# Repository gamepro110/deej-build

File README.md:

# deej-build

| dir | what |
| --- | --- |
| [pcb](<./pcb/>) | pcb design files |
| [µ code](<./µ code/>) | code for the µ (micro) controller |

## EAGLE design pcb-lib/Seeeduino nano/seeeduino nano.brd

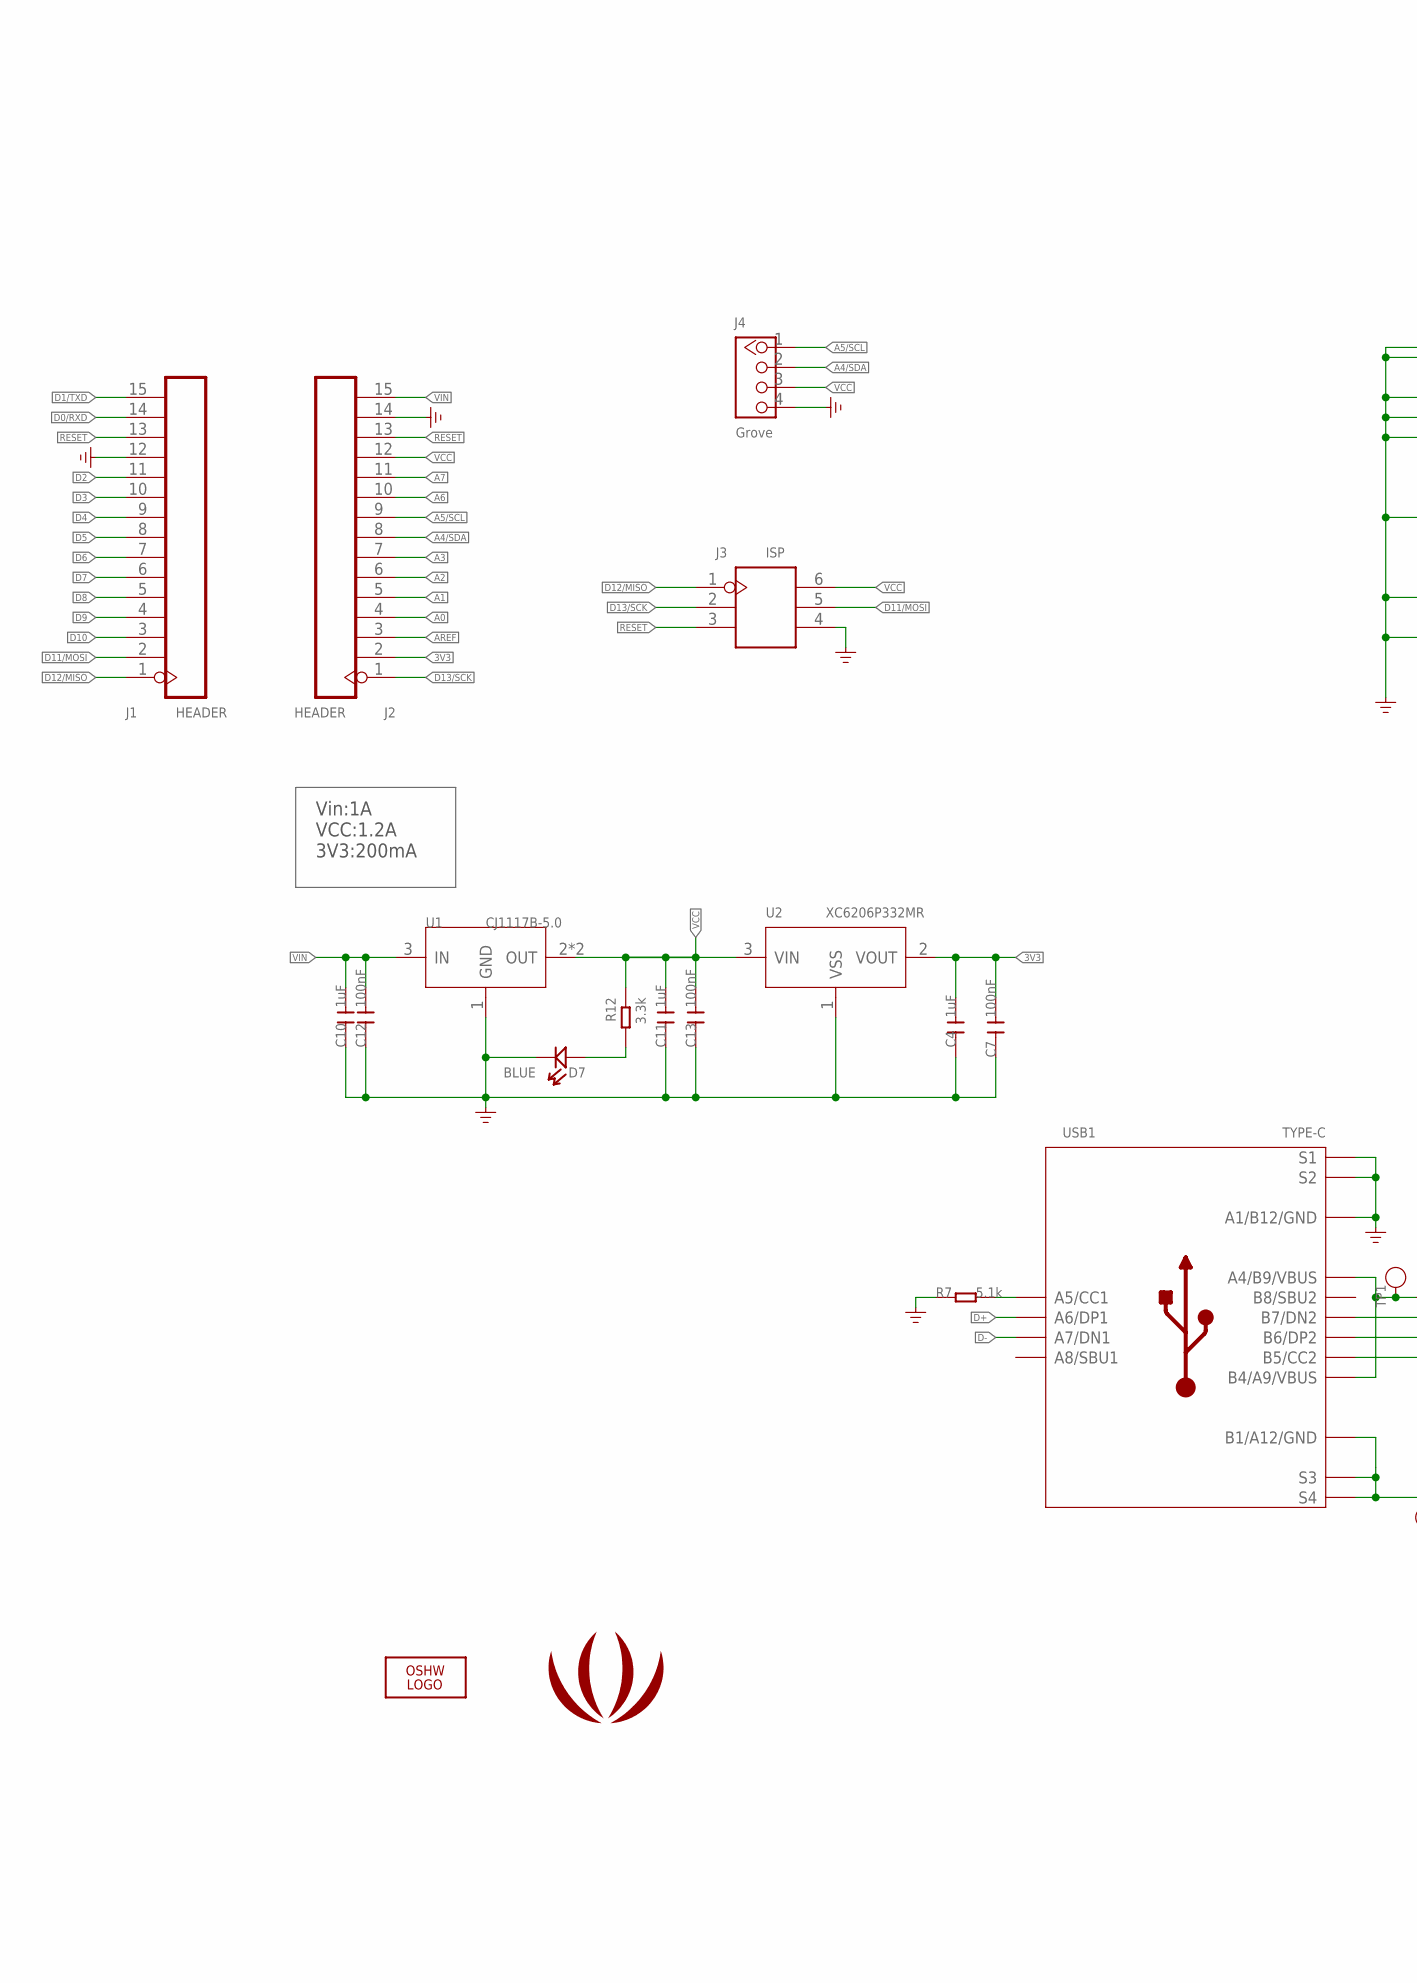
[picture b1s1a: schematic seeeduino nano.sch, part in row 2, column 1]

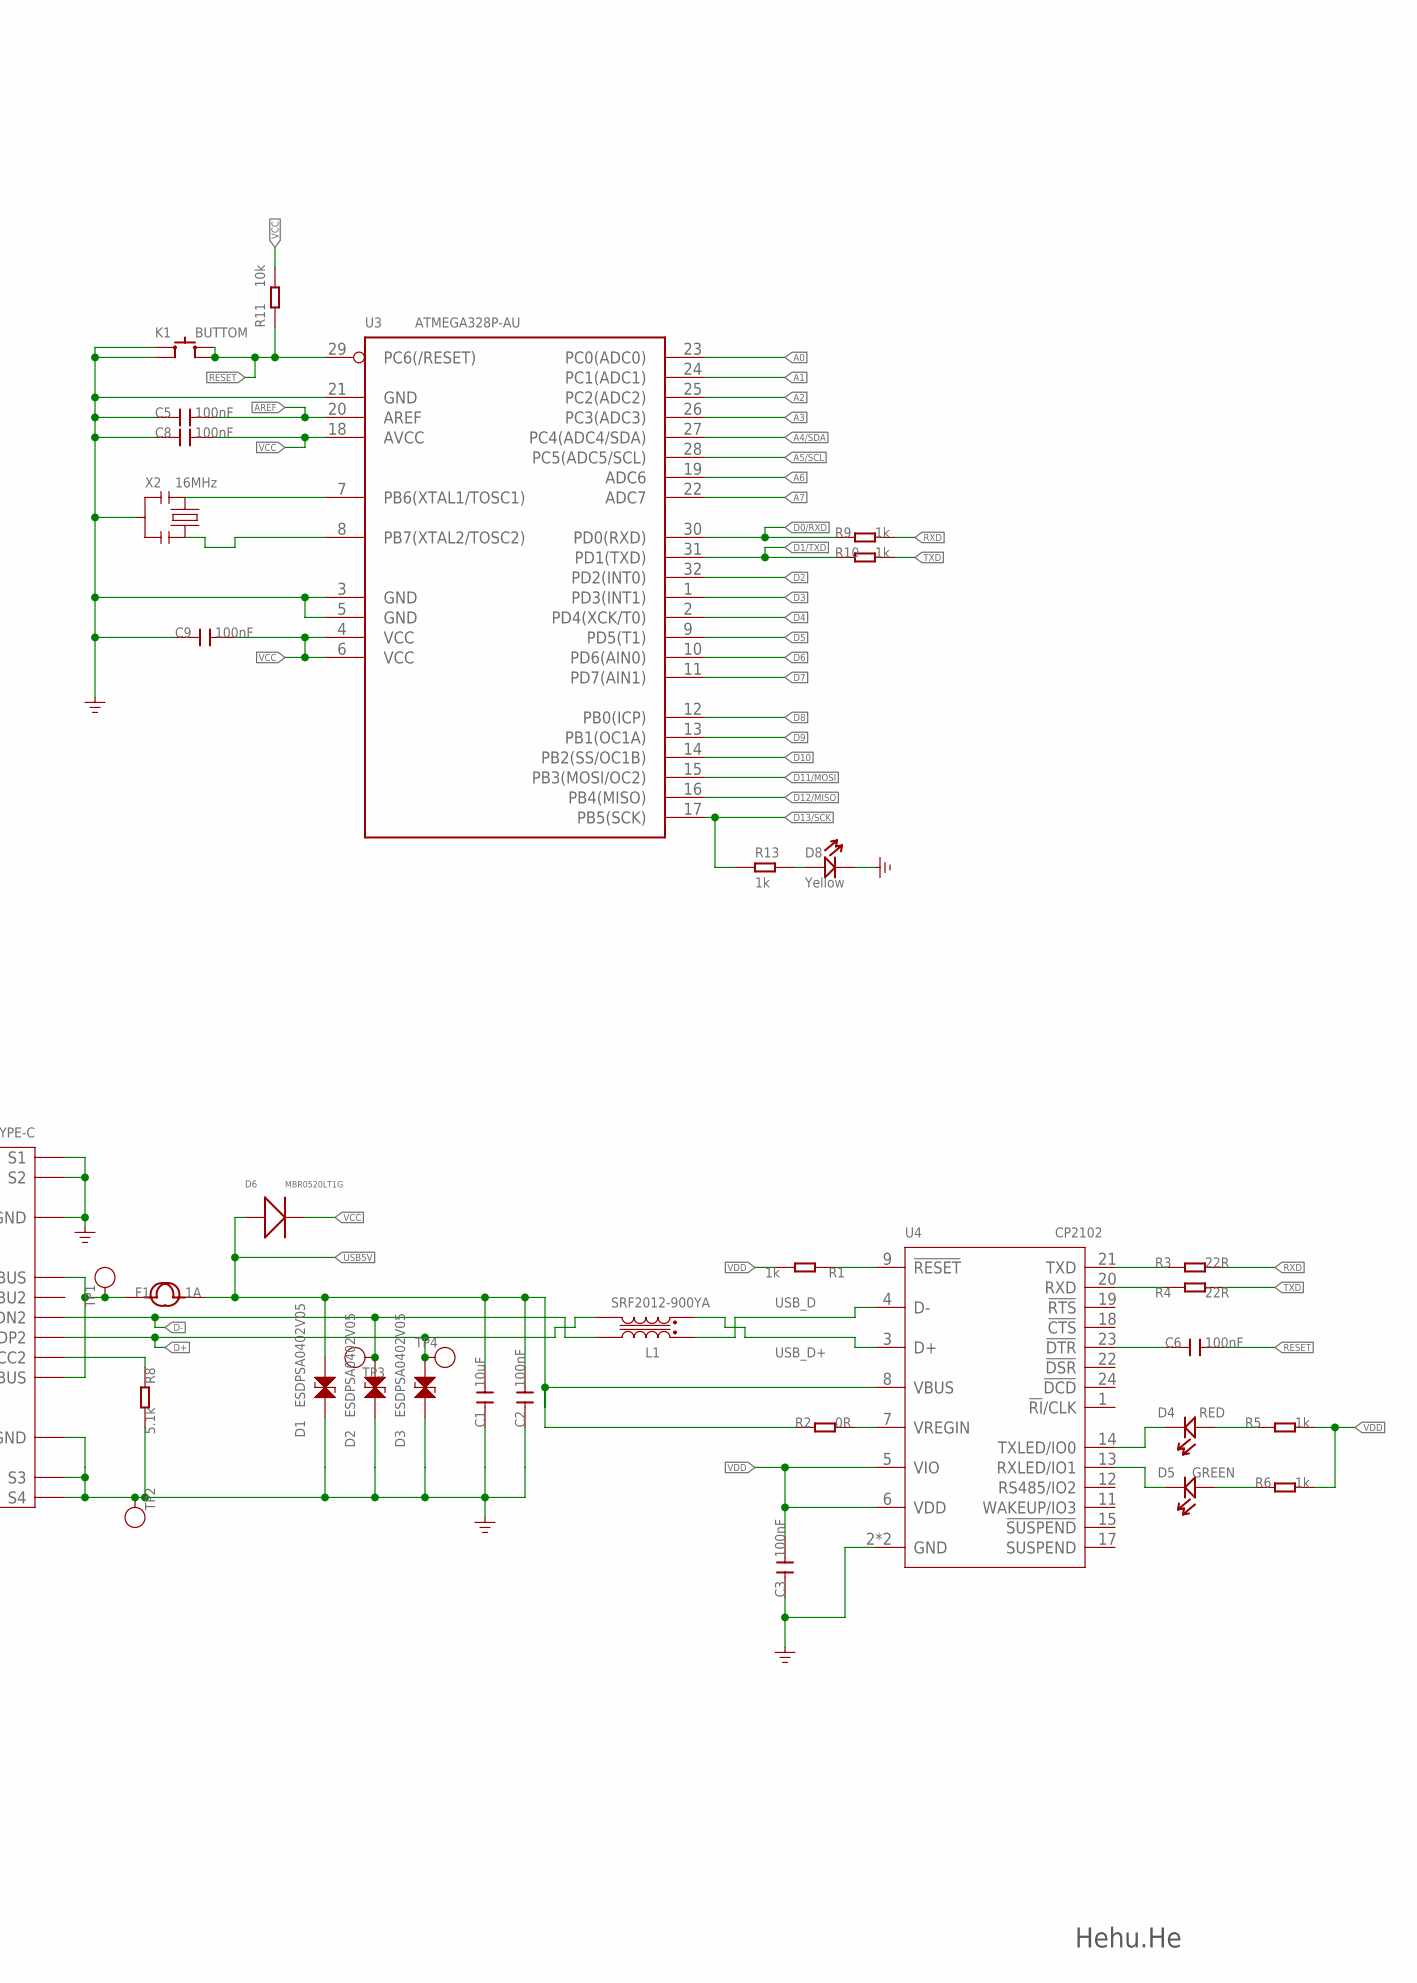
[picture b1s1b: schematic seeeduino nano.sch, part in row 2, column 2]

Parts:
C1: 10uF; C0603
C2, C3, C5, C6, C7, C8, C9, C12, C13: 100nF; C0603
C4, C10, C11: 1uF; C0603
D1, D2, D3: ESDPSA0402V05; ESD-0402
D4: RED; LED-0402
D5: GREEN; LED-0402
D6: MBR0520LT1G; SOD123-2.7X1.6
D7: BLUE; LED-0402
D8: Yellow; LED-0402
F1: 1A; F1206
J1, J2: HEADER; H15-2.54
J3: ISP; H2X3-2.54
J4: Grove; HW4-2.0
K1: BUTTOM; SW4P-SMD-4.5X3.2X2.5MM
L1: SRF2012-900YA; INT4-0.85-2X1.25X1.2MM
LOGO1: LOGO-OSHW-FILLX0100-NT; OSHW_FILLX100_NOTEXT
R1, R5, R6, R9, R10, R13: 1k; R0603
R2: 0R; R0603
R3, R4: 22R; R0603
R7, R8: 5.1k; R0603
R11: 10k; R0603
R12: 3.3k; R0603
TP1, TP2, TP3, TP4: TEST; TP-D45MIL
U1: CJ1117B-5.0; SOT-223
U2: XC6206P332MR; SOT-23
U3: ATMEGA328P-AU; TQFP32-0.8-7X7MM
U4: CP2102; QFN24G-0.5-4X4MM
U$2: LOGO-SEEED-SMALL-SILK; SEEED-SILK--TNAME-160*153MIL
USB1: TYPE-C; USB2.0-TYPE-C
X2: 16MHz; RESONATOR3-SMD-3.6X1.3X0.8MM

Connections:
3V3: C4.1, C7.1, J2.2, U2.2 (VOUT)
A0: J2.4, U3.23 (PC0(ADC0))
A1: J2.5, U3.24 (PC1(ADC1))
A2: J2.6, U3.25 (PC2(ADC2))
A3: J2.7, U3.26 (PC3(ADC3))
A4/SDA: J2.8, J4.2, U3.27 (PC4(ADC4/SDA))
A5/SCL: J2.9, J4.1, U3.28 (PC5(ADC5/SCL))
A6: J2.10, U3.19 (ADC6)
A7: J2.11, U3.22 (ADC7)
AREF: C5.1, J2.3, U3.20 (AREF)
D0/RXD: J1.14, R9.1, U3.30 (PD0(RXD))
D1/TXD: J1.15, R10.1, U3.31 (PD1(TXD))
D2: J1.11, U3.32 (PD2(INT0))
D3: J1.10, U3.1 (PD3(INT1))
D4: J1.9, U3.2 (PD4(XCK/T0))
D5: J1.8, U3.9 (PD5(T1))
D6: J1.7, U3.10 (PD6(AIN0))
D7: J1.6, U3.11 (PD7(AIN1))
D8: J1.5, U3.12 (PB0(ICP))
D9: J1.4, U3.13 (PB1(OC1A))
D10: J1.3, U3.14 (PB2(SS/OC1B))
D11/MOSI: J1.2, J3.5, U3.15 (PB3(MOSI/OC2))
D12/MISO: J1.1, J3.1, U3.16 (PB4(MISO))
D13/SCK: J2.1, J3.2, R13.1, U3.17 (PB5(SCK))
D+: D3.2, L1.3, TP4.T, USB1.A6 (A6/DP1), USB1.B6 (B6/DP2)
D-: D2.2, L1.2, TP3.T, USB1.A7 (A7/DN1), USB1.B7 (B7/DN2)
GND: C1.2, C2.2, C3.2, C4.2, C5.2, C7.2, C8.2, C9.2, C10.2, C11.2, C12.2, C13.2, D1.1, D2.1, D3.1, D7.-, D8.-, J1.12, J2.14, J3.4, J4.4, K1.1 (A0), K1.2 (A1), R7.1, R8.2, TP2.T, U1.1 (GND), U2.1 (VSS), U3.3 (GND), U3.5 (GND), U3.21 (GND), U4.2 (GND), U4.PAD (GND), USB1.A1_B12 (A1/B12/GND), USB1.B1_A12 (B1/A12/GND), USB1.S1, USB1.S2, USB1.S3, USB1.S4, USB1.S5 (S1), USB1.S6 (S2), X2.2
unnamed: R7.2, USB1.A5 (A5/CC1)
unnamed: R8.1, USB1.B5 (B5/CC2)
unnamed: D8.+, R13.2
unnamed: F1.1, TP1.T, USB1.A4_B9 (A4/B9/VBUS), USB1.B4_A9 (B4/A9/VBUS)
unnamed: C6.2, U4.23 (!DTR!)
unnamed: D4.+, R5.1
unnamed: U3.7 (PB6(XTAL1/TOSC1)), X2.1
unnamed: D5.-, U4.13 (RXLED/IO1)
unnamed: U3.8 (PB7(XTAL2/TOSC2)), X2.3
unnamed: D7.+, R12.2
unnamed: D5.+, R6.1
unnamed: D4.-, U4.14 (TXLED/IO0)
unnamed: R4.1, U4.20 (RXD)
unnamed: R3.1, U4.21 (TXD)
unnamed: R2.2, U4.7 (VREGIN)
unnamed: R1.2, U4.9 (!RESET!)
RESET: C6.1, J1.13, J2.13, J3.3, K1.3 (B0), K1.4 (B1), R11.1, U3.29 (PC6(/RESET))
RXD: R3.2, R9.2
TXD: R4.2, R10.2
USB5V: C1.1, C2.1, D1.2, D6.1 (+), F1.2, R2.1, U4.8 (VBUS)
USB_D: L1.1, U4.4 (D-)
USB_D+: L1.4, U4.3 (D+)
VCC: C8.1, C9.1, C11.1, C13.1, D6.2 (-), J2.12, J3.6, J4.3, R11.2, R12.1, U1.2 (OUT), U1.TER (OUT), U2.3 (VIN), U3.4 (VCC), U3.6 (VCC), U3.18 (AVCC)
VDD: C3.1, R1.1, R5.2, R6.2, U4.5 (VIO), U4.6 (VDD)
VIN: C10.1, C12.1, J2.15, U1.3 (IN)

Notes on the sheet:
seeedduino Nano
2019/02/13
Hehu.He
Vin:1A VCC:1.2A 3V3:200mA

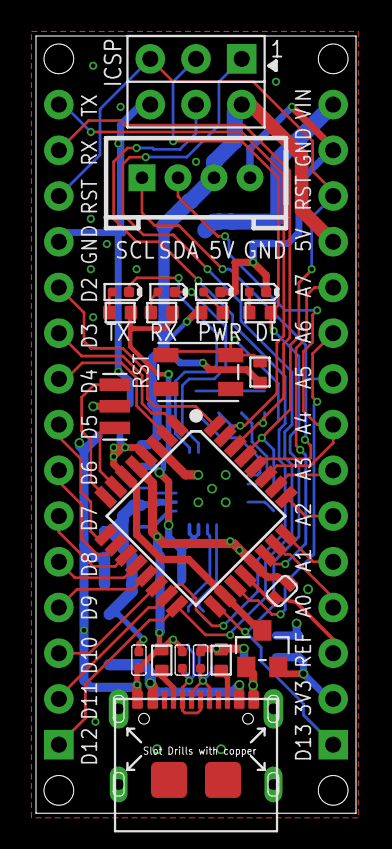
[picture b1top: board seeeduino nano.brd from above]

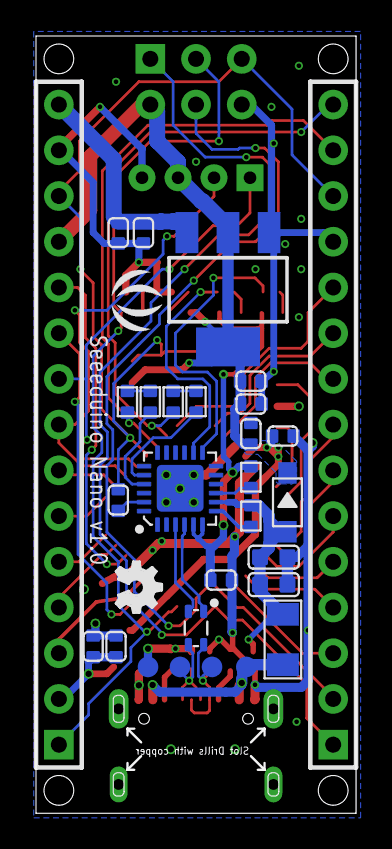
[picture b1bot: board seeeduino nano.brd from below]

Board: 2 copper layers, 17.7 x 43.1 mm, 53 parts (31 on the bottom side), 52 nets.

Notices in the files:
parts and their libraries:
moudle-new: CC-BY-SA
